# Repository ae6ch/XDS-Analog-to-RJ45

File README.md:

6/17/21 - First batch being made at JLCPCB for testing

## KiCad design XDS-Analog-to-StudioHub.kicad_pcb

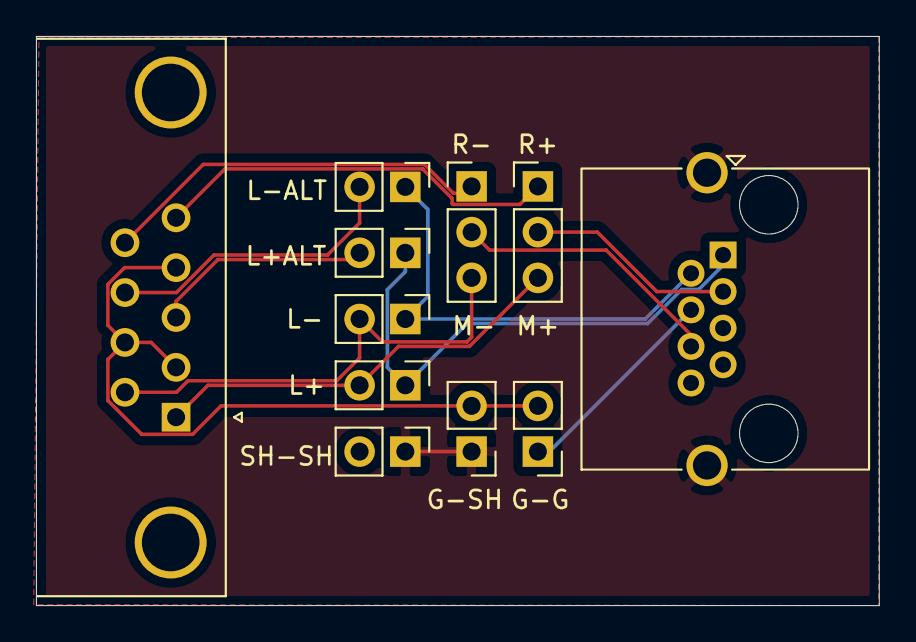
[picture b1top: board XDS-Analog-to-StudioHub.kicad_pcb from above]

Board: 2 copper layers, 46.8 x 31.6 mm, 11 parts (0 on the bottom side), 14 nets.

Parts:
J1: RJ45_Shielded; RJ45_Amphenol_RJHSE5380
J2: DB9_Female; DSUB-9_Female_Horizontal_P2.77x2.84mm_EdgePinOffset4.94mm_H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
JP5: G-G; PinHeader_1x02_P2.54mm_Vertical
JP6: L-; PinHeader_1x02_P2.54mm_Vertical
JP7: L+; PinHeader_1x02_P2.54mm_Vertical
JP8: SH-SH; PinHeader_1x02_P2.54mm_Vertical
JP9: G-SH; PinHeader_1x02_P2.54mm_Vertical
JP10: L-ALT; PinHeader_1x02_P2.54mm_Vertical
JP11: L+ALT; PinHeader_1x02_P2.54mm_Vertical
R+: R+; PinHeader_1x03_P2.54mm_Vertical
R-: R-; PinHeader_1x03_P2.54mm_Vertical

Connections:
unnamed: J1.1, JP7.1, JP11.1
unnamed: J1.2, JP6.1, JP10.1
unnamed: J1.3, R+.2
unnamed: J1.4, JP5.1
unnamed: J1.6, R-.2
unnamed: J1.SH, JP8.1, JP9.1
unnamed: J2.0, JP8.2
unnamed: J2.1, JP7.2, R+.3
unnamed: J2.2, J2.4, J2.7, JP5.2, JP9.2
unnamed: J2.3, JP11.2
unnamed: J2.5, R+.1
unnamed: J2.6, JP6.2, R-.3
unnamed: J2.8, JP10.2
unnamed: J2.9, R-.1

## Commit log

2021-06-16 completed design, added gerber files
2021-06-17 added readme
2021-06-17 added gitignore
2021-07-06 corrected grounding issue
2021-07-22 fixed missing grounds
